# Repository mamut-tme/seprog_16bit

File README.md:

# seprog_16bit
16bit chip adapter for the WG Electronics Seprog programmer

## Info in english:
This repo describes a 16-bit chip adapter for the eprom programmer "Seprog" from the polish manufacturer WG Electronics. The rest will be in polish, because I don't belive that anyone outside of Poland will be interested in this information.

To repozytorium zawiera schemat i płytkę zaprojektowaną w oprogramowaniu Kicad do adaptera do 16-bitowych układów EPROM (tych kasowalnych UV) do programatora Seprog firmy WG Electronics. Schemat opracowałem przez analizę działania mojego programatora z firmware w wersji 1.49 (bardzo możliwe, że niższe wersje oprogramowania nie wspierają tych układów, 1.00 nie wspiera - sprawdzono).

Obsługiwane układy (natywnie, przez programator i oryginalne oprogramowanie), podstawka DIL40:
- 27C1024
- 27C2048
- 27C4096

Mój adapter umożliwia ponadto programowanie, podstawka DIL42:
- 27C160
- 27C322
- 27C400
- 27C800

przez ręczne przełączanie banków pamięci (pomysł z https://github.com/mafe72/27c160-tl866-adapter) używając w oprogramowaniu trybu 27C4096)

## Schemat adaptera:

## Problemy:
- Używając algorytmu INTELIgent programator zasila układ programowany (więc również nasz adapter) napięciem 6,25V (zgodnie z dokumentacją np. AM27C160), co już jest poza specyfikacją układów z serii 74HC. U mnie nawet na HCT działało dobrze i po wielu zapisach układy nie uległy uszkodzeniu, ale trzeba to mieć na uwadze.
- Aplikacja wSeprog napisana przez użytkownika jurex portalu elektroda.pl (https://www.elektroda.pl/rtvforum/topic857189.html) niestety niezupełnie poprawnie obsługuje układy 16 bitowe (konieczna jest zamiana sygnałów Q4 i Q6, tak robi oryginalne oprogramowanie pod DOSa, więc zakładam, że oryginalny adapter też tak miał)
- Wzór płytki nie został póki co sprawdzony w praktyce (mam wykonany prototyp z bankowaniem dla większych układów, ale nie przemyślałem aspektu dźwigienki podstawki ZIF programatora i potrzebne są długie goldpiny, adapter bardzo niestabilnie "siedzi").
- Programowanie jest bardzo powolne - ok. 15 minut na jeden bank "27C4096" i to jest czas dla najszybszego algorytmu INTELIgent

## Jeszcze kilka porad dla startujących z tym programatorem:
- Oryginalna aplikacja pod dosa chodzi bardzo dobrze z emulatorem DOSbox (https://www.dosbox.com/), trzeba tylko przekierować port COM emulatora do rzeczywistego portu komputera (może być adapter na USB, programator używa tylko linii RXD i TXD)
- Przypadki związane z losowymi błędami odczytu i zapisu mogą być spowodowane kiepskim zasilaniem. Powinien wystarczyć zasilacz niestabilizowany, oryginalnie chyba był 9V 500mA. Programator ma własny stabilizator 5V i przetwornicę impulsową (nie zapominajmy, że on obsługuje też bardzo stare EPROMy 21V!)

## Render 3D płytki
dla ciekawych

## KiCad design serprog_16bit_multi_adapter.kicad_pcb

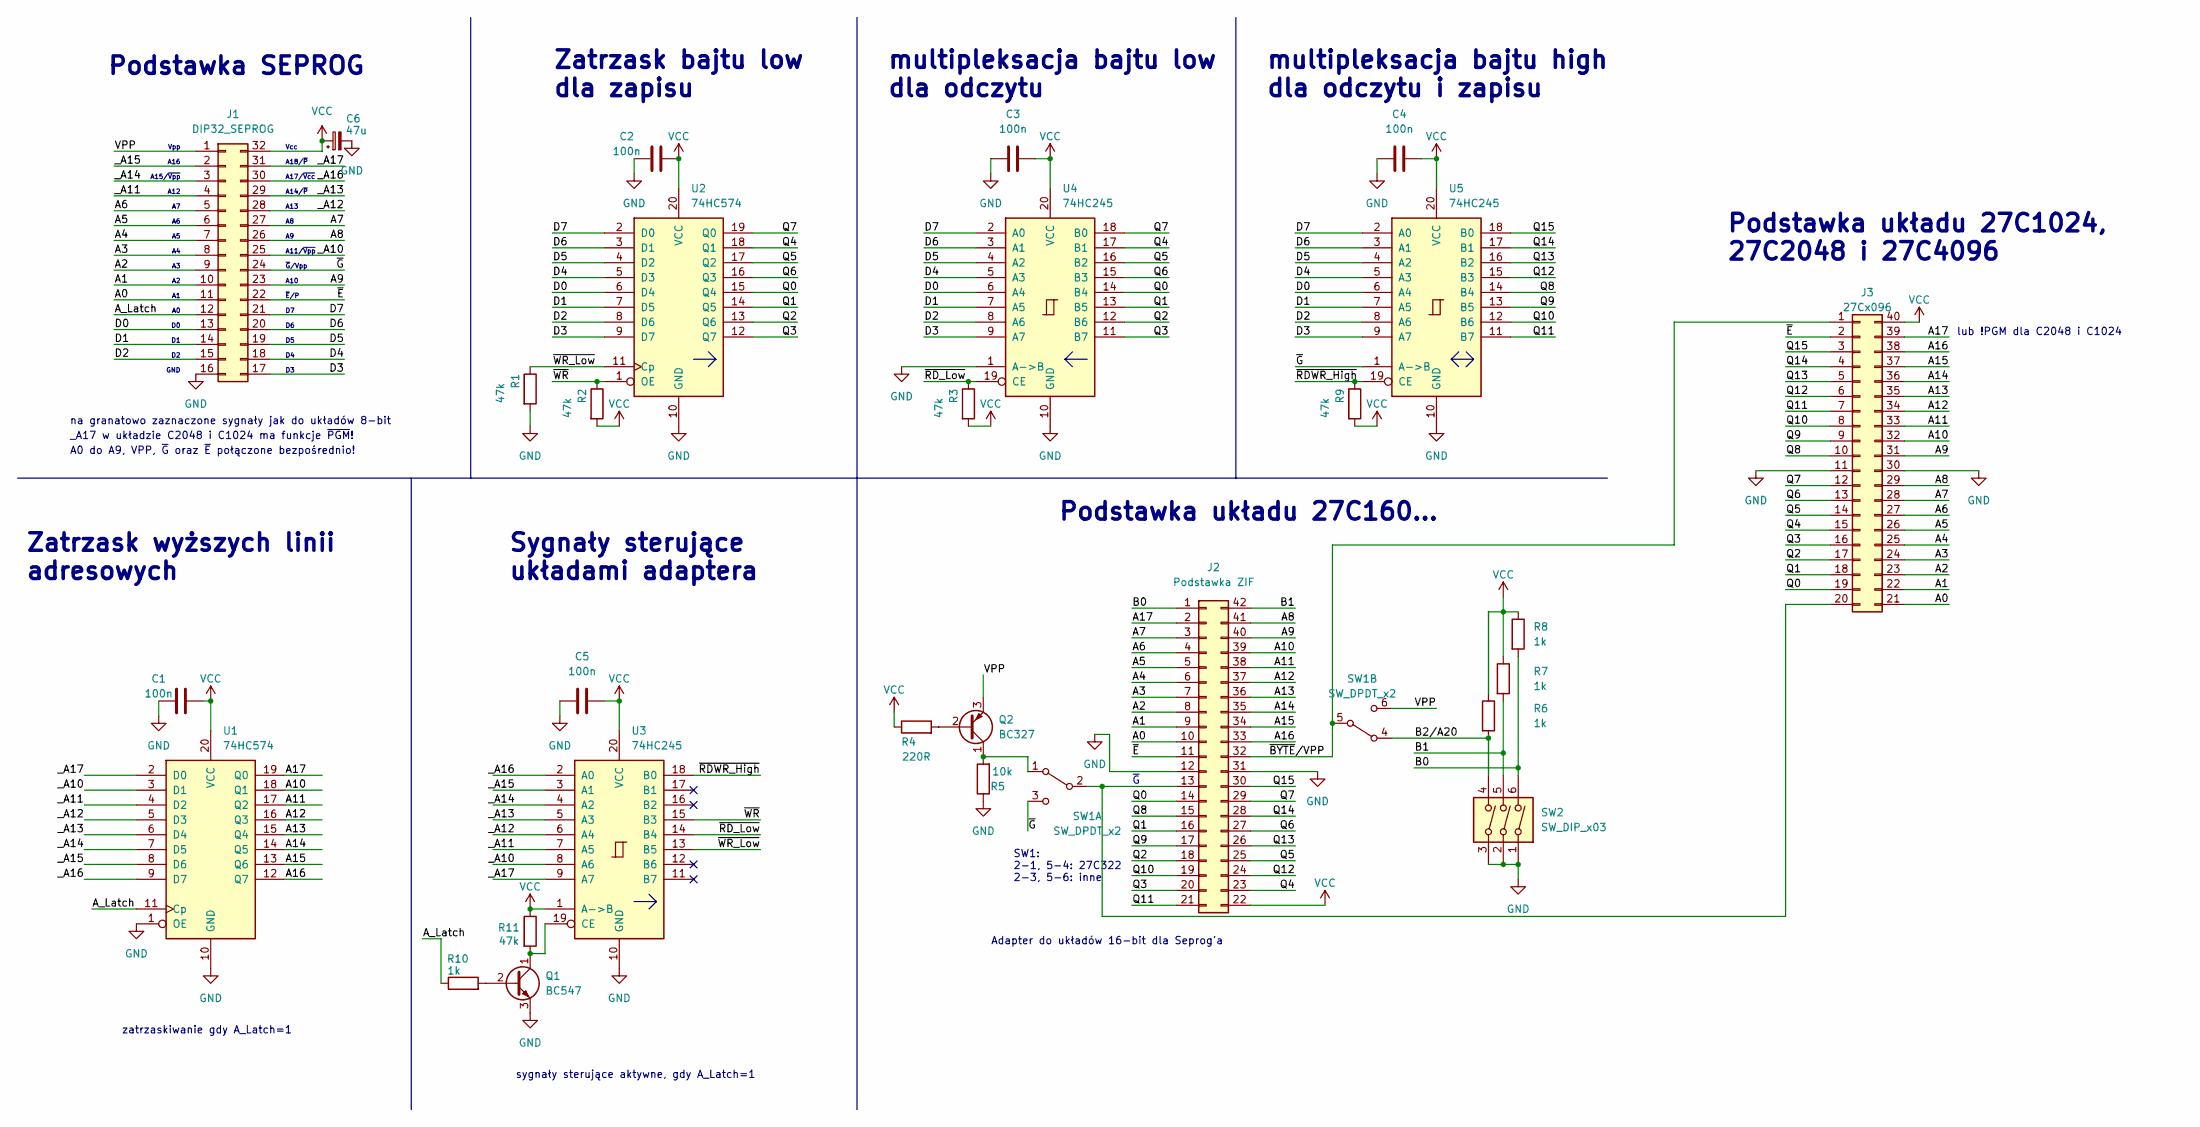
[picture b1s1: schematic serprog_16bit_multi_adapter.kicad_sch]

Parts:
C1, C2, C3, C4, C5: 100n; C_Disc_D3.0mm_W2.0mm_P2.50mm
C6: 47u; CP_Radial_D5.0mm_P2.50mm
J1: DIP32_SEPROG; DIP-32_W15.24mm_Socket_LongPads
J2: Podstawka ZIF; DIP-42_W15.24mm_Socket_LongPads
J3: 27Cx096; DIP-40_W15.24mm_Socket_LongPads
Q1: BC547; TO-92_HandSolder
Q2: BC327; TO-92_HandSolder
R1, R2, R3, R9, R11: 47k; R_Axial_DIN0204_L3.6mm_D1.6mm_P5.08mm_Horizontal
R4: 220R; R_Axial_DIN0204_L3.6mm_D1.6mm_P5.08mm_Horizontal
R5: 10k; R_Axial_DIN0204_L3.6mm_D1.6mm_P5.08mm_Horizontal
R6, R7, R8, R10: 1k; R_Axial_DIN0204_L3.6mm_D1.6mm_P5.08mm_Horizontal
SW1: SW_DPDT_x2; SW_E-Switch_EG1271_SPDT
SW2: SW_DIP_x03; SW_DIP_SPSTx03_Slide_9.78x9.8mm_W7.62mm_P2.54mm
U1, U2: 74HC574; DIP-20_W7.62mm_Socket_LongPads
U3, U4, U5: 74HC245; DIP-20_W7.62mm_Socket_LongPads

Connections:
/A0: J1.11, J2.10, J3.21
/A1: J1.10, J2.9, J3.22
/A2: J1.9, J2.8, J3.23
/A3: J1.8, J2.7, J3.24
/A4: J1.7, J2.6, J3.25
/A5: J1.6, J2.5, J3.26
/A6: J1.5, J2.4, J3.27
/A7: J1.27, J2.3, J3.28
/A8: J1.26, J2.41, J3.29
/A9: J1.23, J2.40, J3.31
/A10: J2.39, J3.32, U1.18 (Q1)
/A11: J2.38, J3.33, U1.17 (Q2)
/A12: J2.37, J3.34, U1.16 (Q3)
/A13: J2.36, J3.35, U1.15 (Q4)
/A14: J2.35, J3.36, U1.14 (Q5)
/A15: J2.34, J3.37, U1.13 (Q6)
/A16: J2.33, J3.38, U1.12 (Q7)
/A17: J2.2, J3.39, U1.19 (Q0)
/A_Latch: J1.12, R10.1, U1.11 (Cp)
/B0: J2.1, R8.2, SW2.6
/B1: J2.42, R7.2, SW2.5
/B2/A20: R6.2, SW1.4 (A), SW2.4
/D0: J1.13, U2.6 (D4), U4.6 (A4), U5.6 (A4)
/D1: J1.14, U2.7 (D5), U4.7 (A5), U5.7 (A5)
/D2: J1.15, U2.8 (D6), U4.8 (A6), U5.8 (A6)
/D3: J1.17, U2.9 (D7), U4.9 (A7), U5.9 (A7)
/D4: J1.18, U2.5 (D3), U4.5 (A3), U5.5 (A3)
/D5: J1.19, U2.4 (D2), U4.4 (A2), U5.4 (A2)
/D6: J1.20, U2.3 (D1), U4.3 (A1), U5.3 (A1)
/D7: J1.21, U2.2 (D0), U4.2 (A0), U5.2 (A0)
/Q0: J2.14, J3.19, U2.15 (Q4), U4.14 (B4)
/Q1: J2.16, J3.18, U2.14 (Q5), U4.13 (B5)
/Q2: J2.18, J3.17, U2.13 (Q6), U4.12 (B6)
/Q3: J2.20, J3.16, U2.12 (Q7), U4.11 (B7)
/Q4: J2.23, J3.15, U2.18 (Q1), U4.17 (B1)
/Q5: J2.25, J3.14, U2.17 (Q2), U4.16 (B2)
/Q6: J2.27, J3.13, U2.16 (Q3), U4.15 (B3)
/Q7: J2.29, J3.12, U2.19 (Q0), U4.18 (B0)
/Q8: J2.15, J3.10, U5.14 (B4)
/Q9: J2.17, J3.9, U5.13 (B5)
/Q10: J2.19, J3.8, U5.12 (B6)
/Q11: J2.21, J3.7, U5.11 (B7)
/Q12: J2.24, J3.6, U5.15 (B3)
/Q13: J2.26, J3.5, U5.16 (B2)
/Q14: J2.28, J3.4, U5.17 (B1)
/Q15: J2.30, J3.3, U5.18 (B0)
/VPP: J1.1, Q2.3 (E), SW1.6 (C)
/_A10: J1.25, U1.3 (D1), U3.8 (A6)
/_A11: J1.4, U1.4 (D2), U3.7 (A5)
/_A12: J1.28, U1.5 (D3), U3.6 (A4)
/_A13: J1.29, U1.6 (D4), U3.5 (A3)
/_A14: J1.3, U1.7 (D5), U3.4 (A2)
/_A15: J1.2, U1.8 (D6), U3.3 (A1)
/_A16: J1.30, U1.9 (D7), U3.2 (A0)
/_A17: J1.31, U1.2 (D0), U3.9 (A7)
/~BYTE/VPP: J2.32, J3.1, SW1.5 (B)
/~E: J1.22, J2.11, J3.2
/~G: J1.24, SW1.3 (C), U5.1 (A->B)
/~RDWR_High: R9.1, U3.18 (B0), U5.19 (CE)
/~RD_Low: R3.1, U3.14 (B4), U4.19 (CE)
/~WR_Low: R1.1, U2.11 (Cp), U3.13 (B5)
/~WR: R2.1, U2.1 (OE), U3.15 (B3)
GND: C1.2, C2.2, C3.2, C4.1, C5.1, C6.2, J1.16, J2.12, J2.31, J3.11, J3.30, Q1.3 (E), R1.2, R5.1, SW2.1, SW2.2, SW2.3, U1.1 (OE), U1.10 (GND), U2.10 (GND), U3.10 (GND), U4.1 (A->B), U4.10 (GND), U5.10 (GND)
unnamed: J2.13, J3.20, SW1.2 (B)
unnamed: Q1.2 (B), R10.2
unnamed: Q1.1 (C), R11.2, U3.19 (CE)
unnamed: Q2.2 (B), R4.2
unnamed: Q2.1 (C), R5.2, SW1.1 (A)
VCC: C1.1, C2.1, C3.1, C4.2, C5.2, C6.1, J1.32, J2.22, J3.40, R2.2, R3.2, R4.1, R6.1, R7.1, R8.1, R9.2, R11.1, U1.20 (VCC), U2.20 (VCC), U3.1 (A->B), U3.20 (VCC), U4.20 (VCC), U5.20 (VCC)

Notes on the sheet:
Vpp A16 A15/~{Vpp} A12 A7 A6 A5 A4 A3 A2 A1 A0 D0 D1 D2 GND
zatrzaskiwanie gdy A_Latch=1
multipleksacja bajtu high dla odczytu i zapisu
Zatrzask wyższych linii adresowych
_A17 w układzie C2048 i C1024 ma funkcje ~{PGM}!
Sygnały sterujące układami adaptera
Podstawka układu 27C160...
Adapter do układów 16-bit dla Seprog'a
Vcc A18/~{P} A17/~{Vcc} A14/~{P} A13 A8 A9 A11/~{Vpp} ~{G}/Vpp A10 ~{E}/P D7 D6 D5 D4 D3
SW1: 2-1, 5-4: 27C322 2-3, 5-6: inne
A0 do A9, VPP, ~{G} oraz ~{E} połączone bezpośrednio!
~{G}
Zatrzask bajtu low dla zapisu
multipleksacja bajtu low dla odczytu
Podstawka układu 27C1024, 27C2048 i 27C4096
sygnały sterujące aktywne, gdy A_Latch=1
lub !PGM dla C2048 i C1024
Podstawka SEPROG
na granatowo zaznaczone sygnały jak do układów 8-bit

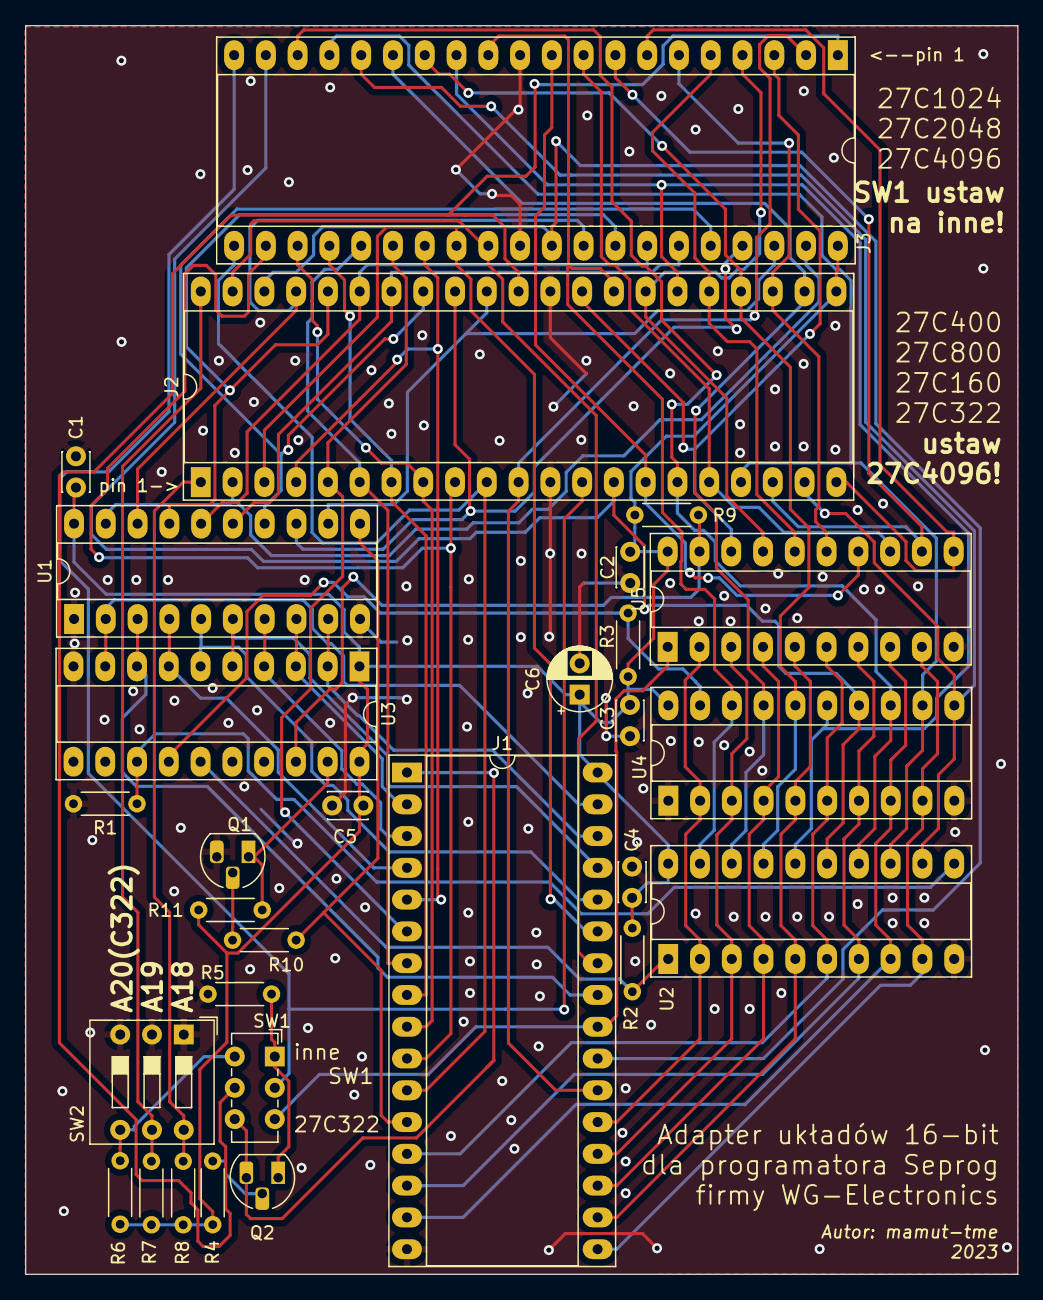
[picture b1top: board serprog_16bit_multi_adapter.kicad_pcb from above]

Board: 2 copper layers, 79.3 x 99.8 mm, 29 parts (0 on the bottom side), 69 nets.

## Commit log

2023-05-17 Update serprog_16bit_multi_adapter.svg
    korekty formatowania etykiet
2023-05-17 Update README.md
    dodano render 3d płytki
2025-06-11 Update README.md
    update on 1.00 FW version not supporting 16 bit chips
